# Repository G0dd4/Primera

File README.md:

# Primera
Robotique project by student in first year engineering school
#

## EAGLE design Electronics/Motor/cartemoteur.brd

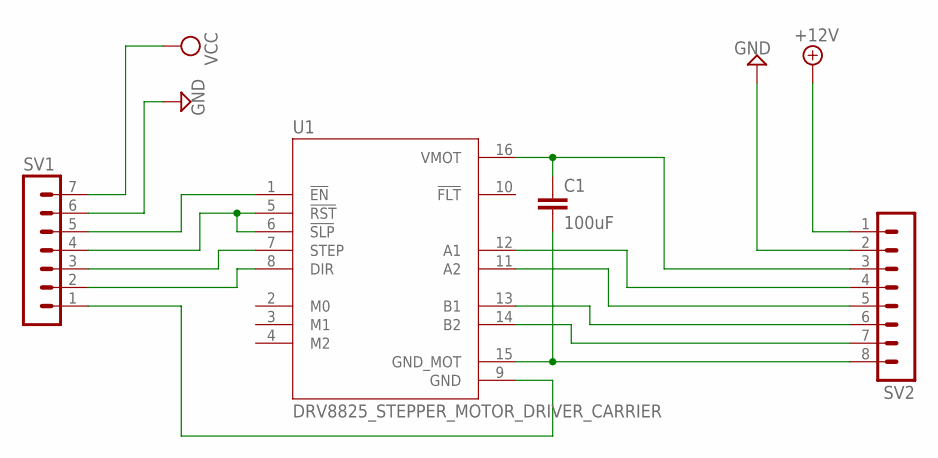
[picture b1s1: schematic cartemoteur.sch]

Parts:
C1: 100uF; C025-024X044
SV1: MA07-1
SV2: MA08-1
U1: DRV8825_STEPPER_MOTOR_DRIVER_CARRIER; IC_DRV8825_STEPPER_MOTOR_DRIVER_CARRIER

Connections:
+12V: SV2.1
GND: SV1.6, SV2.2
unnamed: SV1.5, U1.1 (!EN)
unnamed: SV1.4, U1.5 (!RST), U1.6 (!SLP)
unnamed: SV1.3, U1.7 (STEP)
unnamed: SV1.2, U1.8 (DIR)
unnamed: SV1.1, U1.9 (GND)
unnamed: C1.2, SV2.8, U1.15 (GND_MOT)
unnamed: SV2.7, U1.14 (B2)
unnamed: SV2.6, U1.13 (B1)
unnamed: SV2.5, U1.11 (A2)
unnamed: SV2.4, U1.12 (A1)
unnamed: C1.1, SV2.3, U1.16 (VMOT)
VCC: SV1.7

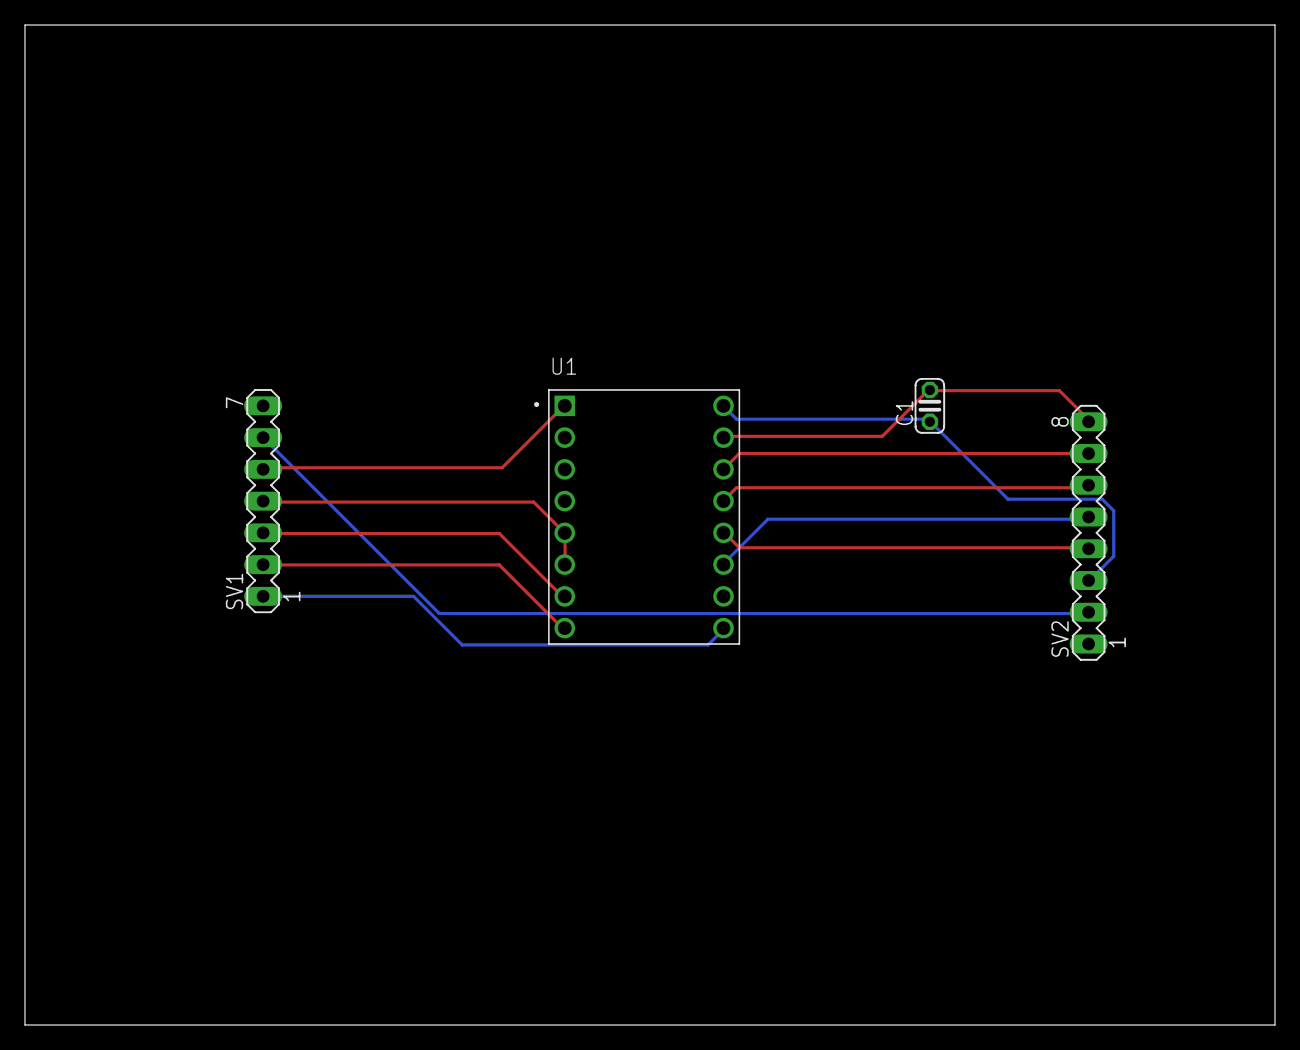
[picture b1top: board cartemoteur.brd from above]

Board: 2 copper layers, 100.0 x 80.0 mm, 4 parts (0 on the bottom side), 12 nets.

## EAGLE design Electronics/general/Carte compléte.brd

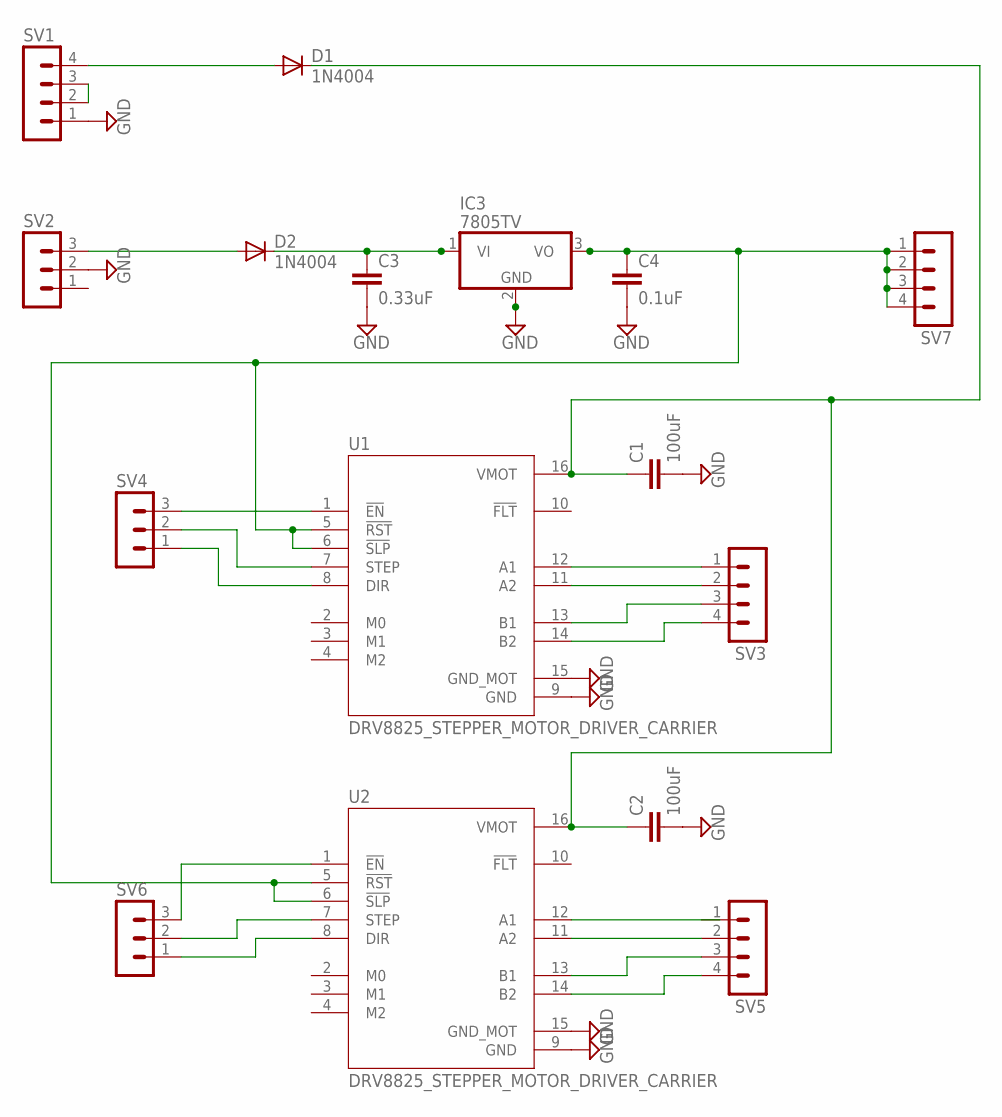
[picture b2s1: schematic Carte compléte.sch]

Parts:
C1, C2: 100uF; C025-024X044
C3: 0.33uF; C025-024X044
C4: 0.1uF; C025-024X044
D1, D2: 1N4004; DO41-10
IC3: 7805TV; TO220V
SV1, SV3, SV5, SV7: MA04-1
SV2, SV4, SV6: MA03-1
U1, U2: DRV8825_STEPPER_MOTOR_DRIVER_CARRIER; IC_DRV8825_STEPPER_MOTOR_DRIVER_CARRIER

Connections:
GND: C1.2, C2.2, C3.2, C4.2, IC3.2 (GND), SV1.1, SV2.2, U1.9 (GND), U1.15 (GND_MOT), U2.9 (GND), U2.15 (GND_MOT)
unnamed: C3.1, D2.C, IC3.1 (VI)
unnamed: SV4.2, U1.7 (STEP)
unnamed: C4.1, IC3.3 (VO), SV7.1, SV7.2, SV7.3, SV7.4, U1.5 (!RST), U1.6 (!SLP), U2.5 (!RST), U2.6 (!SLP)
unnamed: D1.A, SV1.4
unnamed: SV1.2, SV1.3
unnamed: D2.A, SV2.3
unnamed: SV4.3, U1.1 (!EN)
unnamed: SV3.1, U1.12 (A1)
unnamed: SV3.2, U1.11 (A2)
unnamed: SV3.3, U1.13 (B1)
unnamed: SV3.4, U1.14 (B2)
unnamed: C1.1, C2.1, D1.C, U1.16 (VMOT), U2.16 (VMOT)
unnamed: SV4.1, U1.8 (DIR)
unnamed: SV5.2, U2.11 (A2)
unnamed: SV5.3, U2.13 (B1)
unnamed: SV5.4, U2.14 (B2)
unnamed: SV6.3, U2.1 (!EN)
unnamed: SV6.2, U2.7 (STEP)
unnamed: SV6.1, U2.8 (DIR)

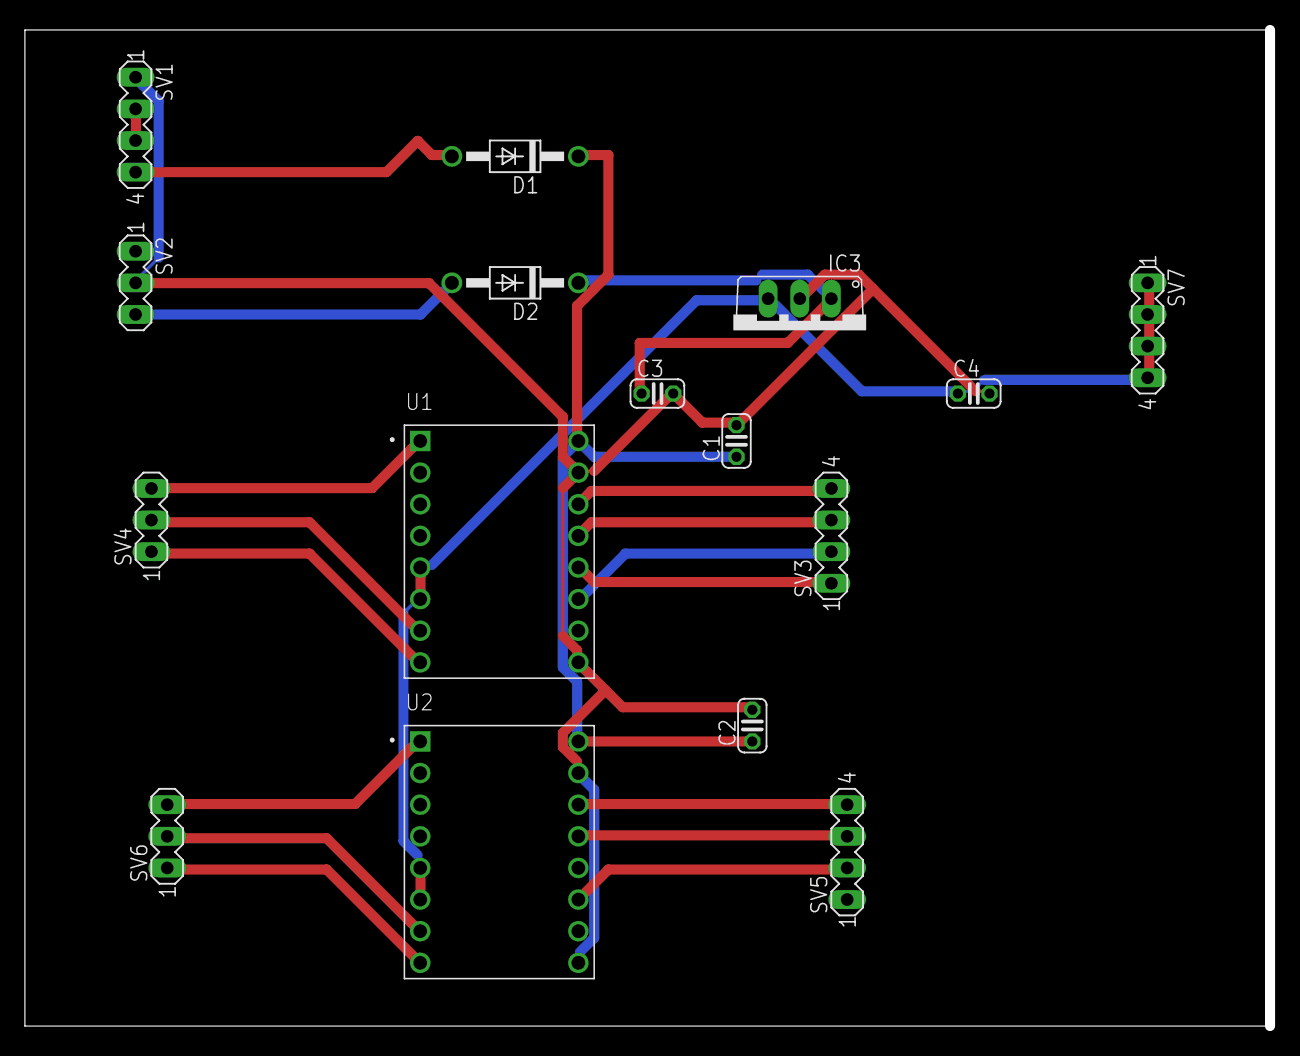
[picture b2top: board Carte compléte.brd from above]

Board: 2 copper layers, 100.0 x 80.0 mm, 16 parts (0 on the bottom side), 20 nets.

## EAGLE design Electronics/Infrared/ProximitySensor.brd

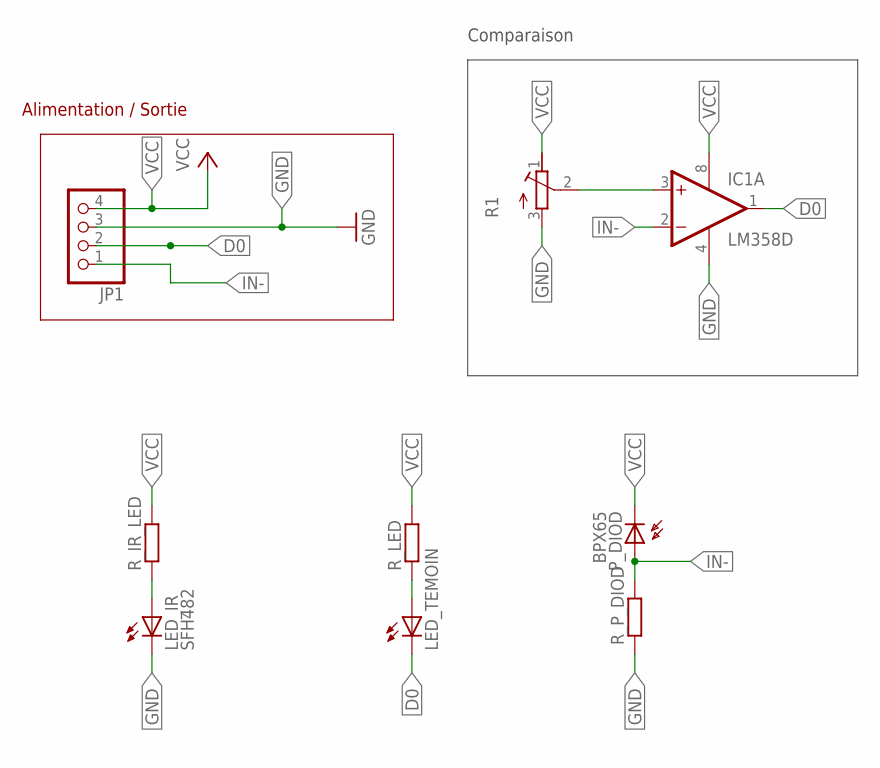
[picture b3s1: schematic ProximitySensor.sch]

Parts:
IC1: LM358D; SO08
JP1: PINHD-1X4M; 1X04M
LED_IR: SFH482
LED_TEMOIN: LEDSMT1206; 1206
P_DIOD: BPX65
R1: R-TRIMMT93YA; RTRIMT93YA
R_IR_LED: RR1206; R1206
R_LED: RR1206; R1206
R_P_DIOD: RR1206; R1206

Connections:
D0: IC1.1 (OUT), JP1.2, LED_TEMOIN.C
GND: IC1.4 (V-), JP1.3, LED_IR.K (C), R1.3 (A), R_P_DIOD.1
IN-: IC1.2 (-IN), JP1.1, P_DIOD.A, R_P_DIOD.2
unnamed: LED_IR.A, R_IR_LED.1
unnamed: IC1.3 (+IN), R1.2 (S)
unnamed: LED_TEMOIN.A, R_LED.1
VCC: IC1.8 (V+), JP1.4, P_DIOD.K (C), R1.1 (E), R_IR_LED.2, R_LED.2

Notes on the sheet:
Alimentation / Sortie
Comparaison

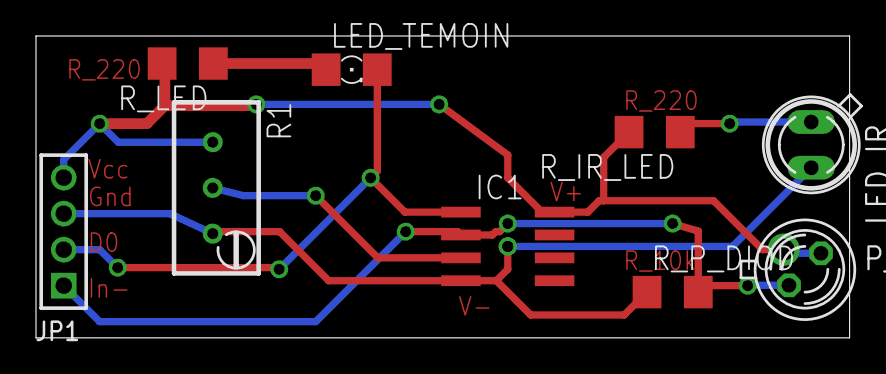
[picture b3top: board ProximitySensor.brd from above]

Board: 2 copper layers, 45.2 x 16.8 mm, 9 parts (0 on the bottom side), 7 nets.

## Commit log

2020-03-23 Create d
2020-03-23 Create Motor
2020-04-06 modification de la carte (trimmer CMS en trimmer THT)
2020-04-06 ajout des commentaire |amélioration de la class DRV8825
2020-04-10 Installation driver | Installation Library
2020-04-17 Création de la view Prog
2020-04-17 Création de la view programmation
2020-04-18 modification de progView | Création de la view Labi
2020-04-18 modification de interface.h
2020-04-27 Ajout detection d'erreur et correction erreur
2020-05-11 Création de la view calcul | Finalisation de la vérification | Supression des warnings
2020-05-11 Création de la view calcul
2020-05-31 Create Color Sensor
2020-06-04 trie du projet et ajout de tous les fichier
